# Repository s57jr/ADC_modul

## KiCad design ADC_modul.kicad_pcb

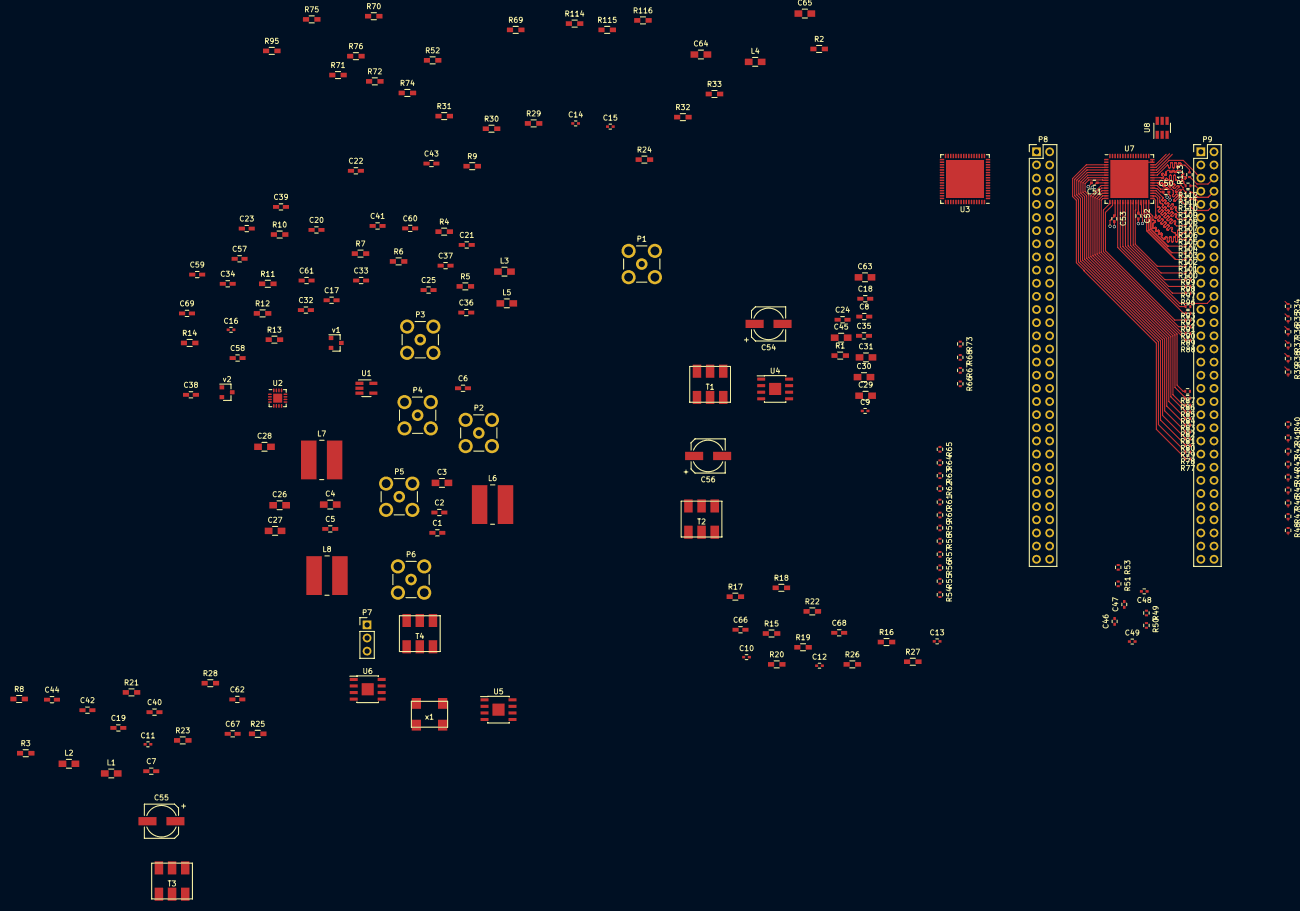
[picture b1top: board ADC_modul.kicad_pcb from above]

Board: 2 copper layers, 216 parts (0 on the bottom side), 220 nets.

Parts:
C1, C2, C5, C6, C7, C17, C19, C20, C21, C22, C23, C24, C25, C32, C33, C34, C35, C38, C39, C40, C41, C42, C43, C44, C57, C58, C59, C62, C66, C67, C68, C69: 100n; C_0603_HandSoldering
C3, C4, C30, C31: 10u; C_0805_HandSoldering
C8, C18: 10n; C_0603_HandSoldering
C9, C10, C11, C12, C13, C14, C15, C16: 40p; C_0402
C26, C27, C28, C29: 4.7u; C_0805_HandSoldering
C36, C60: 1u; C_0603_HandSoldering
C37, C61: 0.1u; C_0603_HandSoldering
C45: 22u; C_0805_HandSoldering
C46, C47, C48, C49, C50, C51, C52, C53: 100n; C_0402
C54, C55, C56: 22u; CP_Elec_6.3x5.3
C63, C64, C65: 1u; C_0805_HandSoldering
L1, L2, L3, L4, L5: 820n; C_0805_HandSoldering
L6, L7, L8: 100u; Choke_SMD_Wuerth-WE-PD2-Typ-L
P1, P2, P3, P4: BNC; SMB_Straight
P5: clk_out; SMB_Straight
P6: ext. clk; SMB_Straight
P7: ext_clk_enable; Pin_Header_Straight_1x03_Pitch2.54mm
P8: a/b; Pin_Header_Straight_2x32_Pitch2.54mm
P9: CONN_02X32; Pin_Header_Straight_2x32_Pitch2.54mm
R1, R2, R3, R4, R5, R7, R8, R9, R10: 50; R_0603_HandSoldering
R6, R76, R114: 10k; R_0603_HandSoldering
R11, R12, R13, R14, R15, R16, R17, R18, R22, R24, R25, R26, R27: 33; R_0603_HandSoldering
R19: 2k; R_0603_HandSoldering
R20, R21: R_Small; R_0603_HandSoldering
R23: 0; R_0603_HandSoldering
R28, R29, R30, R31: 150; R_0603_HandSoldering
R32, R33: 100; R_0603_HandSoldering
R34, R37, R38, R39, R40, R41, R42, R43, R44, R45, R46, R47, R48, R49, R50, R51, R53, R56, R57, R58, R59, R60, R61, R62, R63, R64, R65, R66, R67, R68, R73, R77, R80, R81, R82, R83, R84, R85, R86, R87, R88, R89, R90, R91, R92, R93, R96, R97, R100, R101, R102, R103, R104, R105, R106, R107, R108, R109, R110, R111, R112, R113: 22; R_0402
R35, R36, R54, R55, R78, R79, R98, R99: DNI; R_0402
R52, R95: 10k_1%; R_0603_HandSoldering
R69: 30k(1%); R_0603_HandSoldering
R70: 24k(1%); R_0603_HandSoldering
R71, R74: (1%)30k; R_0603_HandSoldering
R72, R75: (1%)24k; R_0603_HandSoldering
R115, R116: 4.7k; R_0603_HandSoldering
T1, T2, T3, T4: ADT1-1WT; adt1-1wt
U1: BUF602IDBVT; SOT-23-5_HandSoldering
U2: CDCLVP1102; UQFN-16-1EP_3x3mm_Pitch0.5mm
U3: AD9648_2; QFN-64-1EP_9x9mm_Pitch0.5mm
U4, U5, U6: BD00HC0WEFJ; SOIC-8-1EP_3.9x4.9mm_Pitch1.27mm
U7: AD9648_1; QFN-64-1EP_9x9mm_Pitch0.5mm
U8: SN74LVC2G07; SOT-23-6_Handsoldering
v1, v2: ISL21080; SOT-23
x1: cr_oscillator; S73305

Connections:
+3V3: C2.2, C3.2, C4.2, C5.2, C6.2, C20.1, C21.1, R6.2, U1.5, U2.5, v1.1, v2.1, x1.4
/1_AIN+: C9.1, R11.1, U7.51
/1_AIN-: C10.1, R12.1, U7.52
/1_BIN+: C11.1, R13.1, U7.62
/1_BIN-: C12.1, R14.1, U7.61
/1_D0(16bit): R78.2, U7.4
/1_D0B: R80.2, U7.6
/1_D1(16bit): R79.2, U7.5
/1_D1B: R81.2, U7.7
/1_D2B: R82.2, U7.8
/1_D3B: R83.2, U7.9
/1_D4B: R84.2, U7.11
/1_D5A: R105.2, U7.33
/1_D5B: R85.2, U7.12
/1_D6A: R106.2, U7.34
/1_D6B: R86.2, U7.13
/1_D7A: R107.2, U7.35
/1_D7B: R87.2, U7.14
/1_D8A: R108.2, U7.36
/1_D8B: R88.2, U7.15
/1_D9A: R109.2, U7.38
/1_D9B: R89.2, U7.16
/1_D10A: R110.2, U7.39
/1_D11A: R111.2, U7.40
/1_D12A: R112.2, U7.41
/1_D13A: R113.2, U7.42
/2_AIN+: C13.1, R15.1, U3.51
/2_AIN-: C14.1, R16.1, U3.52
/2_BIN+: C15.1, R17.1, U3.62
/2_BIN-: C16.1, R18.1, U3.61
/2_D0(16bit): R35.2, U3.4
/2_D0B: R37.2, U3.6
/2_D1(16bit): R36.2, U3.5
/2_D1B: R38.2, U3.7
/2_D2B: R39.2, U3.8
/2_D3B: R40.2, U3.9
/2_D4B: R41.2, U3.11
/2_D5A: R61.2, U3.33
/2_D5B: R42.2, U3.12
/2_D6A: R62.2, U3.34
/2_D6B: R43.2, U3.13
/2_D7A: R63.2, U3.35
/2_D7B: R44.2, U3.14
/2_D8A: R64.2, U3.36
/2_D8B: R45.2, U3.15
/2_D9A: R65.2, U3.38
/2_D9B: R46.2, U3.16
/2_D10A: R66.2, U3.39
/2_D11A: R67.2, U3.40
/2_D12A: R68.2, U3.41
/2_D13A: R73.2, U3.42
/CLK_1+: C32.1, R32.1, U7.1
/CLK_1-: C33.1, R32.2, U7.2
/CLK_2+: C35.1, R33.2, U3.1
/CLK_2-: C34.1, R33.1, U3.2
/VCM1: C30.2, L2.1, L3.1, U7.57
/VCM2: C31.2, L4.1, L5.1, U3.57
/cs1: R114.2, U7.46
/cs2: R76.2, U3.46
/sclk: U3.45, U7.45
/sdo: R116.2, U8.4
GND: C9.2, C10.2, C11.2, C12.2, C13.2, C14.2, C15.2, C16.2, C22.1, C23.1, C26.1, C27.1, C30.1, C42.2, C54.2, C57.1, C60.1, C61.1, C62.2, C63.2, C66.2, C67.2, C68.2, P1.2, P2.2, R1.2, R2.2, R70.2, R95.1, T1.2, T2.2, U4.3, U7.47, U7.48, U7.56, U7.65
GNDA: C24.1, C25.1, C28.1, C29.1, C31.1, C36.1, C37.1, C38.2, C39.2, C40.2, C41.2, C43.2, C55.2, C58.1, C64.2, P3.2, P4.2, R3.2, R4.2, R52.1, R72.2, T3.2, T4.2, U3.47, U3.48, U3.56, U3.65, U5.3
GNDD: C1.2, C2.1, C3.1, C4.1, C5.1, C6.1, C8.1, C18.1, C20.2, C21.2, C44.2, C45.1, C46.2, C47.2, C48.2, C49.2, C50.2, C51.2, C52.2, C53.2, C56.2, C59.1, C65.2, C69.1, P5.2, P6.2, P7.3, R21.2, R28.1, R29.2, R30.1, R31.2, R75.2, U1.2, U2.1, U2.16, U6.3, U8.2, v1.3, v2.3, x1.2
GNDPWR: P8.3, P8.4
unnamed: C1.1, R19.1, U1.3
unnamed: C7.1, P6.1
unnamed: C7.2, R20.2
unnamed: C8.2, R22.2, v1.2
unnamed: C17.1, x1.3
unnamed: C17.2, R23.2
unnamed: C18.2, U2.7, v2.2
unnamed: C19.1, R19.2, U1.4
unnamed: C19.2, L1.1, R20.1, R21.1, R23.1, U2.6
unnamed: C22.2, C26.2, R24.2, T1.4
unnamed: C23.2, C27.2, R25.2, T2.4
unnamed: C24.2, C28.2, R26.2, T3.4
unnamed: C25.2, C29.2, R27.2, T4.4
unnamed: C32.2, R28.2, U2.9
unnamed: C33.2, R29.1, U2.10
unnamed: C34.2, R30.2, U2.12
unnamed: C35.2, R31.1, U2.11
unnamed: C36.2, C37.2, U3.55
unnamed: C54.1, C57.2, L6.2, U4.5, U4.8
unnamed: C55.1, C58.2, L7.2, U5.5, U5.8
unnamed: C56.1, C59.2, L8.2, U6.5, U6.8
unnamed: C60.2, C61.2, U7.55
unnamed: C63.1, C64.1, C65.1, L6.1, L7.1, L8.1, P8.1, P8.2
unnamed: L1.2, R22.1
unnamed: L2.2, R24.1
unnamed: L3.2, R25.1
unnamed: L4.2, R26.1
unnamed: L5.2, R27.1
unnamed: P1.1, R1.1, T1.1
unnamed: P2.1, R2.1, T2.1
unnamed: P3.1, R3.1, T3.1
unnamed: P4.1, R4.1, T4.1
unnamed: P5.1, R5.1
unnamed: P7.1, R6.1
unnamed: P7.2, x1.1
unnamed: P8.22, R34.1
unnamed: P8.23, U3.43
unnamed: P8.24, R35.1
unnamed: P8.25, R73.1
unnamed: P8.26, R36.1
unnamed: P8.27, R68.1
unnamed: P8.28, R37.1
unnamed: P8.29, R67.1
unnamed: P8.30, R38.1
unnamed: P8.31, R66.1
unnamed: P8.32, R39.1
unnamed: P8.39, R65.1
unnamed: P8.40, R40.1
unnamed: P8.41, R64.1
unnamed: P8.42, R41.1
unnamed: P8.43, R63.1
unnamed: P8.44, R42.1
unnamed: P8.45, R62.1
unnamed: P8.46, R43.1
unnamed: P8.47, R61.1
unnamed: P8.48, R44.1
unnamed: P8.49, R60.1
unnamed: P8.50, R45.1
unnamed: P8.51, R59.1
unnamed: P8.52, R46.1
unnamed: P8.53, R58.1
unnamed: P8.54, R47.1
unnamed: P8.55, R57.1
unnamed: P8.56, R48.1
unnamed: P8.57, R56.1
unnamed: P8.58, U3.22
unnamed: P8.59, R55.1
unnamed: P8.60, R49.1
unnamed: P8.61, R54.1
unnamed: P8.62, R50.1
unnamed: P8.63, R53.1
unnamed: P8.64, R51.1
unnamed: P9.5, U7.43
unnamed: P9.6, R113.1
unnamed: P9.7, R112.1
unnamed: P9.8, R111.1
unnamed: P9.9, R110.1
unnamed: P9.10, R109.1
unnamed: P9.11, R108.1
unnamed: P9.12, R107.1
unnamed: P9.13, R106.1
unnamed: P9.14, R105.1
unnamed: P9.15, R104.1
unnamed: P9.16, R103.1
unnamed: P9.17, R102.1
unnamed: P9.18, R101.1
unnamed: P9.19, R100.1
unnamed: P9.20, R99.1
unnamed: P9.21, R98.1
unnamed: P9.22, R97.1
unnamed: P9.23, R96.1
unnamed: P9.24, U7.22
unnamed: P9.25, R93.1
unnamed: P9.26, R92.1
unnamed: P9.27, R91.1
unnamed: P9.28, R90.1
unnamed: P9.29, R89.1
unnamed: P9.30, R88.1
unnamed: P9.37, R87.1
unnamed: P9.38, R86.1
unnamed: P9.39, R85.1
unnamed: P9.40, R84.1
unnamed: P9.41, R83.1
unnamed: P9.42, R82.1
unnamed: P9.43, R81.1
unnamed: P9.44, R80.1
unnamed: P9.45, R79.1
unnamed: P9.46, R78.1
unnamed: P9.47, R77.1
unnamed: R5.2, U1.1
unnamed: R10.1, R17.2, T4.5
unnamed: R10.2, R18.2, T4.3
unnamed: R7.1, R11.2, T1.5
unnamed: R7.2, R12.2, T1.3
unnamed: R8.1, R13.2, T2.5
unnamed: R8.2, R14.2, T2.3
unnamed: R9.1, R15.2, T3.5
unnamed: R9.2, R16.2, T3.3
unnamed: R34.2, U3.3
unnamed: R47.2, U3.17
unnamed: R48.2, U3.18
unnamed: R49.2, U3.20
unnamed: R50.2, U3.21
unnamed: R51.2, U3.23
unnamed: R52.2, U3.58
unnamed: R53.2, U3.24
unnamed: R54.2, U3.25
unnamed: R55.2, U3.26
unnamed: R56.2, U3.27
unnamed: R57.2, U3.29
unnamed: R58.2, U3.30
unnamed: R59.2, U3.31
unnamed: R60.2, U3.32
unnamed: R69.2, R70.1, U4.2
unnamed: R71.2, R72.1, U5.2
unnamed: R74.2, R75.1, U6.2
unnamed: R77.2, U7.3
unnamed: R90.2, U7.17
unnamed: R91.2, U7.18
unnamed: R92.2, U7.20
unnamed: R93.2, U7.21
unnamed: R95.2, U7.58
unnamed: R96.2, U7.23
unnamed: R97.2, U7.24
unnamed: R98.2, U7.25
unnamed: R99.2, U7.26
unnamed: R100.2, U7.27
unnamed: R101.2, U7.29
unnamed: R102.2, U7.30
unnamed: R103.2, U7.31
unnamed: R104.2, U7.32
unnamed: R115.2, U3.44, U7.44, U8.3, U8.6
VCC: C38.1, C39.1, C40.1, C41.1, C43.1, R71.1, U3.49, U3.50, U3.53, U3.54, U3.59, U3.60, U3.63, U3.64, U5.1
VDD: C44.1, C45.2, C46.1, C47.1, C48.1, C49.1, C50.1, C51.1, C52.1, C53.1, C69.2, R74.1, R76.1, R114.1, R115.1, R116.1, U3.10, U3.19, U3.28, U3.37, U6.1, U7.10, U7.19, U7.28, U7.37, U8.5
VDDA: C42.1, C62.1, C66.1, C67.1, C68.1, R69.1, U4.1, U7.49, U7.50, U7.53, U7.54, U7.59, U7.60, U7.63, U7.64

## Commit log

2017-01-15 Adding new files
2017-04-16 verilog
